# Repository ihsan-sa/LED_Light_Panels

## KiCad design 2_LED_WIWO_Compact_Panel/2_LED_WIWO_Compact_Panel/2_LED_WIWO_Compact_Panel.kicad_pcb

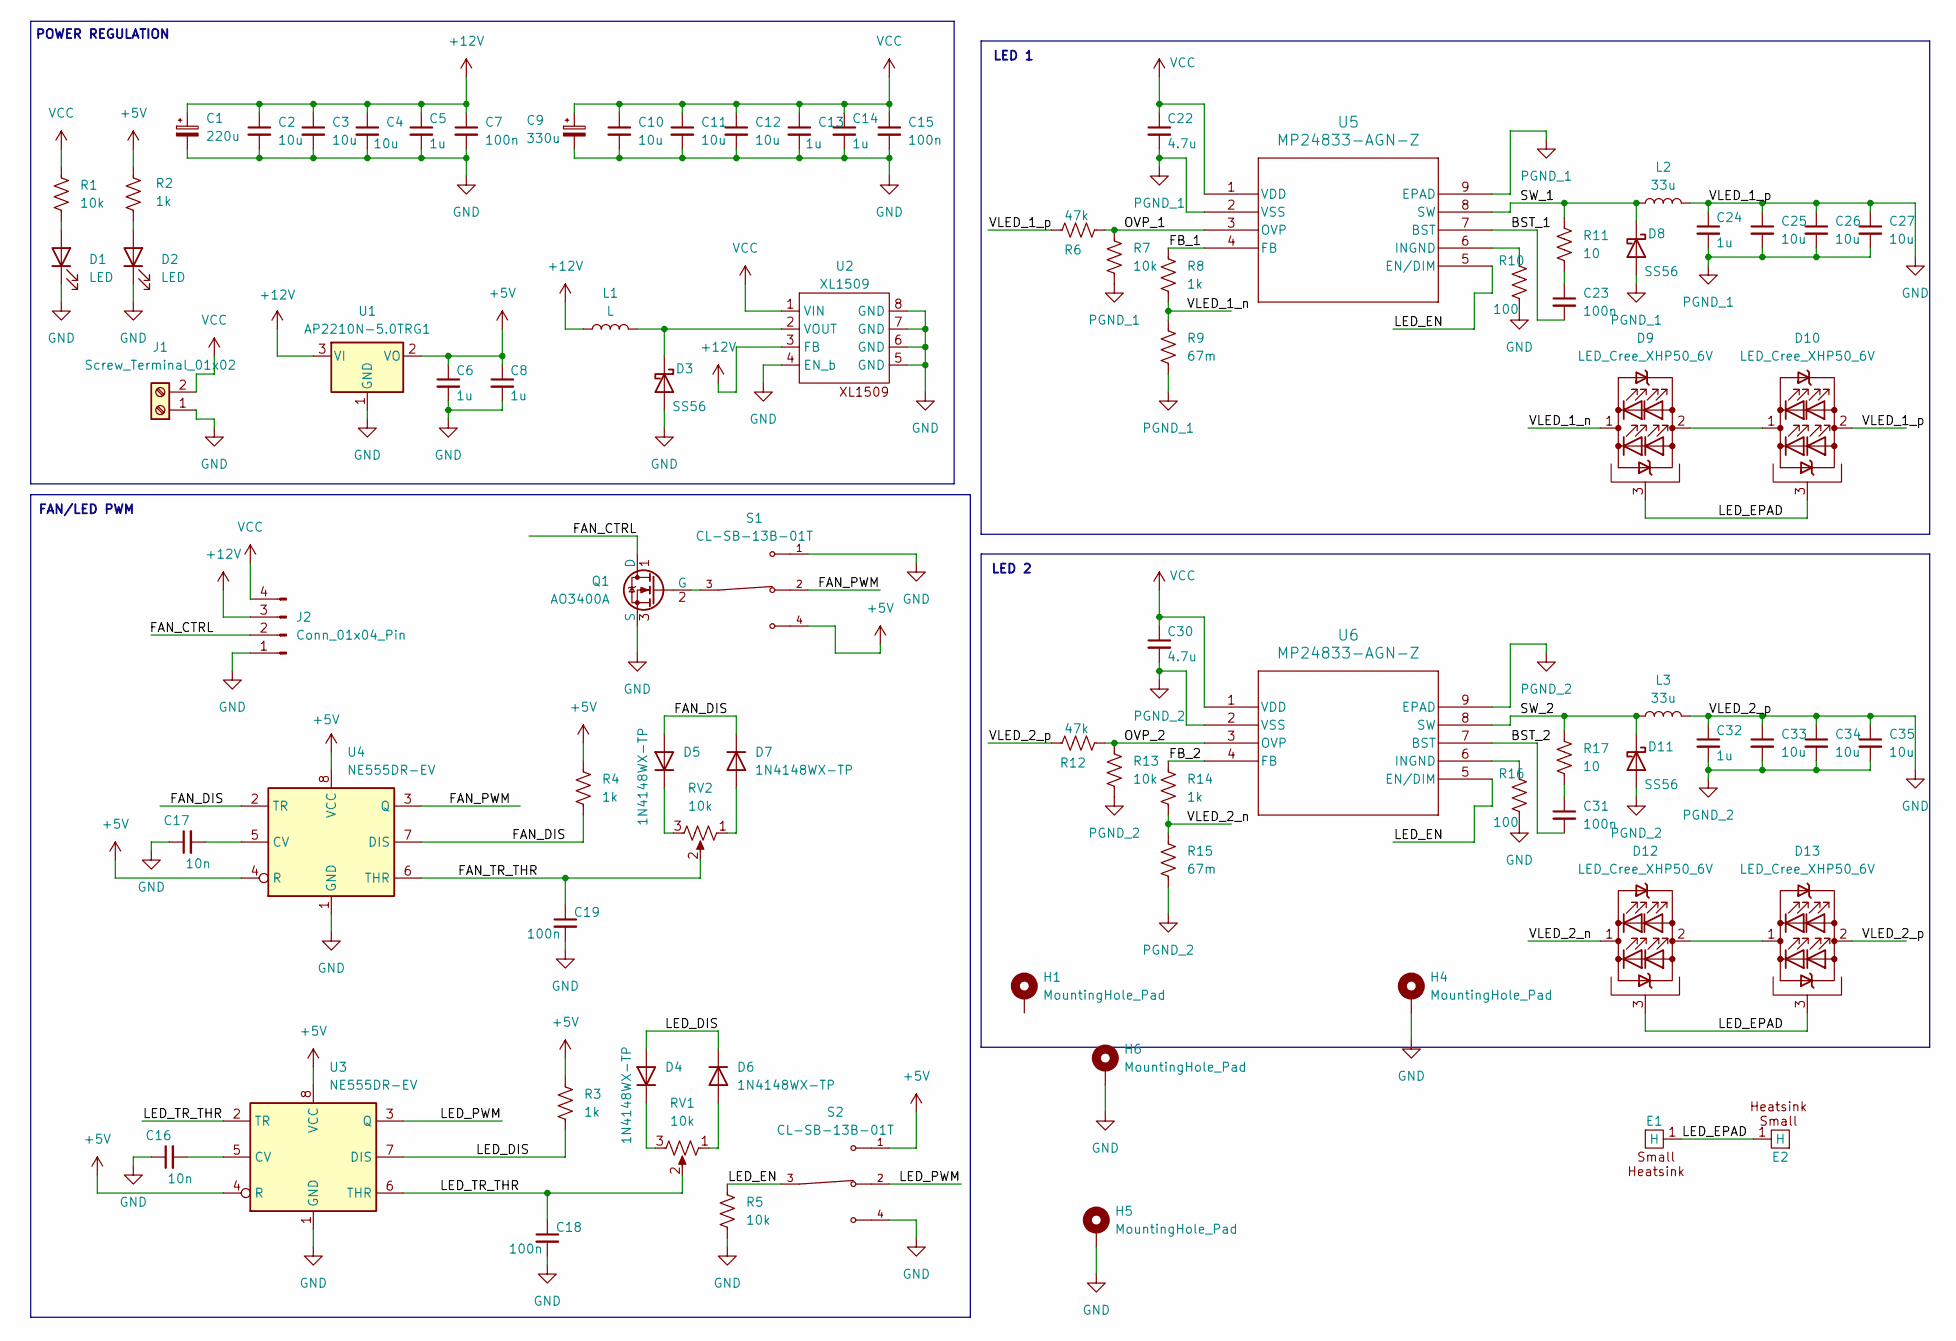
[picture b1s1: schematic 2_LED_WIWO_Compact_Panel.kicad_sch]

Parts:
C1: 220u; CAP_6.3 X 7.7_PAN
C2, C3, C4, C10, C11, C12, C25, C26, C27, C33, C34, C35: 10u; C_0603_1608Metric_Pad1.08x0.95mm_HandSolder
C5, C6, C8, C13, C14: 1u; C_0402_1005Metric_Pad0.74x0.62mm_HandSolder
C7, C15: 100n; C_0201_0603Metric_Pad0.64x0.40mm_HandSolder
C9: 330u; CAPAE1030X1050N
C16, C17: 10n; R_0201_0603Metric_Pad0.64x0.40mm_HandSolder
C18, C19: 100n; R_0402_1005Metric_Pad0.72x0.64mm_HandSolder
C22, C30: 4.7u; C_0603_1608Metric_Pad1.08x0.95mm_HandSolder
C23, C31: 100n; C_0603_1608Metric_Pad1.08x0.95mm_HandSolder
C24, C32: 1u; C_0603_1608Metric_Pad1.08x0.95mm_HandSolder
D1, D2: LED; LED_0603_1608Metric_Pad1.05x0.95mm_HandSolder
D3, D8, D11: SS56; D_SMA_Handsoldering
D4, D5, D6, D7: 1N4148WX-TP; D_SOD-323_HandSoldering
D9, D10, D12, D13: LED_Cree_XHP50_6V; LED_Cree-XHP50_6V
E1, E2: small_heatsink
H1, H4, H5, H6: MountingHole_Pad; MountingHole_3.2mm_M3_Pad
J1: Screw_Terminal_01x02; TerminalBlock_MaiXu_MX126-5.0-02P_1x02_P5.00mm
J2: Conn_01x04_Pin; PinHeader_1x04_P2.54mm_Vertical
L1: L; CDRH127L125NP-680MC
L2, L3: 33u; IND_SRP1265A-330M
Q1: AO3400A; SOT-23_Handsoldering
R1, R5, R7, R13: 10k; R_0402_1005Metric_Pad0.72x0.64mm_HandSolder
R2, R3, R4, R8, R14: 1k; R_0402_1005Metric_Pad0.72x0.64mm_HandSolder
R6, R12: 47k; R_0402_1005Metric_Pad0.72x0.64mm_HandSolder
R9, R15: 67m; R_2512_6332Metric_Pad1.40x3.35mm_HandSolder
R10, R16: 100; R_0603_1608Metric_Pad0.98x0.95mm_HandSolder
R11, R17: 10; R_0603_1608Metric_Pad0.98x0.95mm_HandSolder
RV1, RV2: 10k; PTV09A-4015F-B104_BRN
S1, S2: CL-SB-13B-01T; SW_CL-SB-13B-01T; PARTREV N/A
U1: AP2210N-5.0TRG1; TSOT-23
U2: XL1509; SOIC-8_3.9x4.9mm_P1.27mm
U3, U4: NE555DR-EV; SOIC-8_3.9x4.9mm_P1.27mm
U5, U6: MP24833-AGN-Z; SOIC-8-1EP_3.9x4.9mm_P1.27mm_EP2.514x3.2mm_ThermalVias

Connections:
+5V: C6.1, C8.1, R2.1, R3.1, R4.1, S1.4, S2.1, U1.2 (VO), U3.4 (R), U3.8 (VCC), U4.4 (R), U4.8 (VCC)
+12V: C1.1, C2.1, C3.1, C4.1, C5.1, C7.1, J2.3, L1.1, U1.3 (VI), U2.3 (FB)
/BST_1: C23.2, U5.7 (BST)
/BST_2: C31.2, U6.7 (BST)
/FAN_CTRL: J2.2, Q1.1 (D)
/FAN_DIS: D5.2 (A), D7.1 (K), R4.2, U4.2 (TR), U4.7 (DIS)
/FAN_PWM: S1.2, U4.3 (Q)
/FAN_TR_THR: C19.1, RV2.2, U4.6 (THR)
/FB_1: R8.1, U5.4 (FB)
/FB_2: R14.1, U6.4 (FB)
/LED_DIS: D4.2 (A), D6.1 (K), R3.2, U3.7 (DIS)
/LED_EN: R5.1, S2.3, U5.5 (EN/DIM), U6.5 (EN/DIM)
/LED_EPAD: D9.3 (PAD), D10.3 (PAD), D12.3 (PAD), D13.3 (PAD), E1.1 (H), E2.1 (H)
/LED_PWM: S2.2, U3.3 (Q)
/LED_TR_THR: C18.1, RV1.2, U3.2 (TR), U3.6 (THR)
/OVP_1: R6.2, R7.1, U5.3 (OVP)
/OVP_2: R12.2, R13.1, U6.3 (OVP)
/SW_1: D8.1 (K), L2.1, R11.1, U5.8 (SW)
/SW_2: D11.1 (K), L3.1, R17.1, U6.8 (SW)
/VLED_1_n: D9.1 (K), R8.2, R9.1
/VLED_2_n: D12.1 (K), R14.2, R15.1
GND: C1.2, C2.2, C3.2, C4.2, C5.2, C6.2, C7.2, C8.2, C9.2, C10.2, C11.2, C12.2, C13.2, C14.2, C15.2, C16.1, C17.1, C18.2, C19.2, C24.1, C25.1, C26.1, C27.1, C32.1, C33.1, C34.1, C35.1, D1.1 (K), D2.1 (K), D3.2 (A), D10.2 (A), D13.2 (A), H4.1, H5.1, H6.1, J1.1, J2.1, L2.2, L3.2, Q1.3 (S), R5.2, R6.1, R10.2, R12.1, R16.2, S1.1, S2.4, U1.1 (GND), U2.4 (EN_b), U2.5 (GND), U2.6 (GND), U2.7 (GND), U2.8 (GND), U3.1 (GND), U4.1 (GND)
unnamed: C23.1, R11.2
unnamed: C31.1, R17.2
unnamed: D1.2 (A), R1.2
unnamed: D2.2 (A), R2.2
unnamed: D3.1 (K), L1.2, U2.2 (VOUT)
unnamed: D4.1 (K), RV1.3
unnamed: D5.1 (K), RV2.3
unnamed: D6.2 (A), RV1.1
unnamed: D7.2 (A), RV2.1
unnamed: D9.2 (A), D10.1 (K)
unnamed: D12.2 (A), D13.1 (K)
unnamed: Q1.2 (G), S1.3
unnamed: C16.2, U3.5 (CV)
unnamed: C17.2, U4.5 (CV)
unnamed: R10.1, U5.6 (INGND)
unnamed: R16.1, U6.6 (INGND)
PGND_1: C22.2, C24.2, C25.2, C26.2, C27.2, D8.2 (A), R7.2, R9.2, U5.2 (VSS), U5.9 (EPAD)
PGND_2: C30.2, C32.2, C33.2, C34.2, C35.2, D11.2 (A), R13.2, R15.2, U6.2 (VSS), U6.9 (EPAD)
VCC: C9.1, C10.1, C11.1, C12.1, C13.1, C14.1, C15.1, C22.1, C30.1, J1.2, J2.4, R1.1, U2.1 (VIN), U5.1 (VDD), U6.1 (VDD)

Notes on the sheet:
FAN/LED PWM
LED 1
LED 2
POWER REGULATION

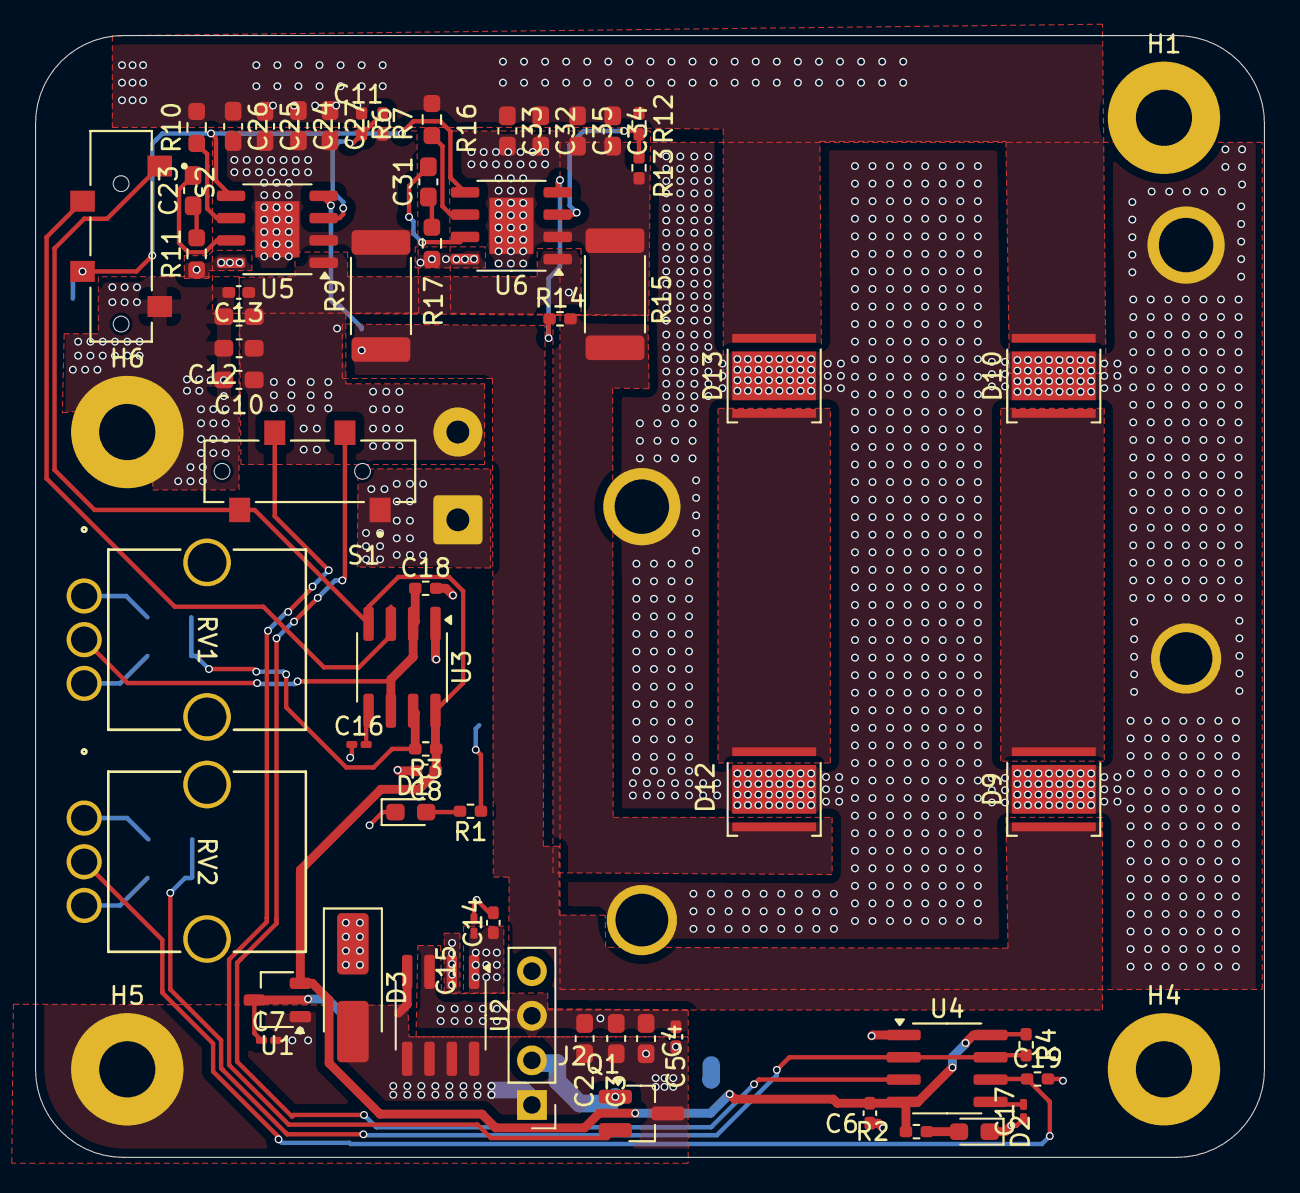
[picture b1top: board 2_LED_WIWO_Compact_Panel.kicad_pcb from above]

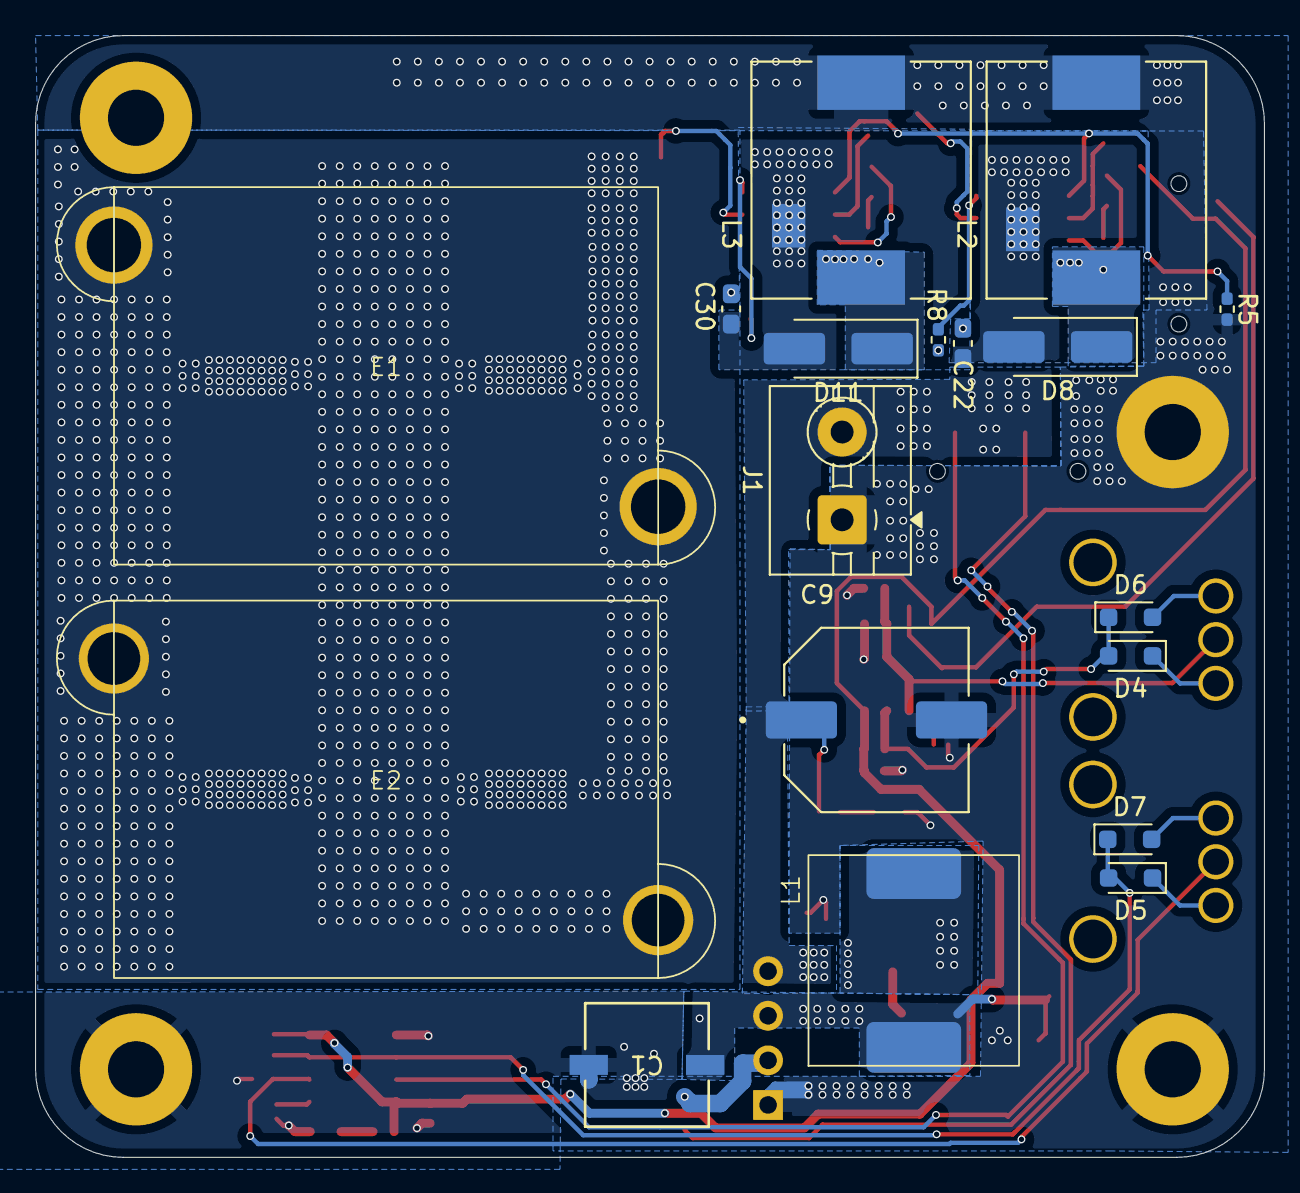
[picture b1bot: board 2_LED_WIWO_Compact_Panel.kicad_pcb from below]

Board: 2 copper layers, 70.0 x 63.9 mm, 83 parts (18 on the bottom side), 41 nets.

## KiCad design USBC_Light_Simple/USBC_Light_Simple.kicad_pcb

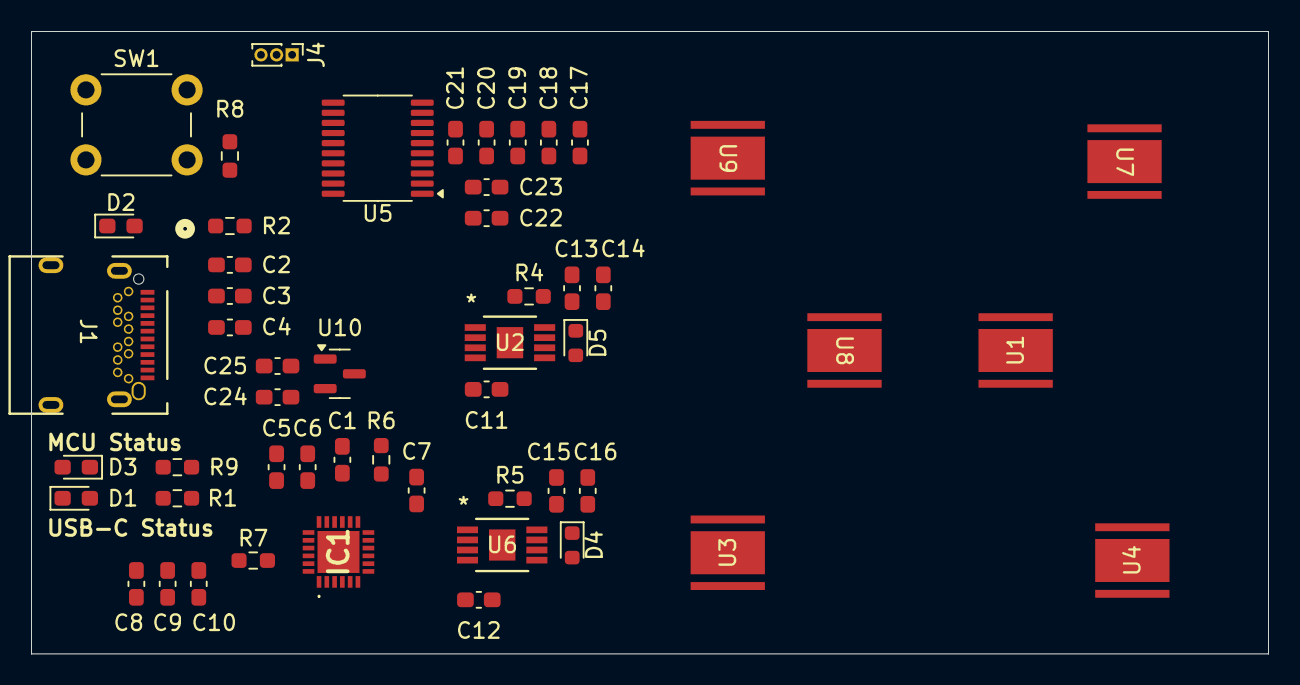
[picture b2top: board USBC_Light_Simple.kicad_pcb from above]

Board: 2 copper layers, 79.5 x 40.0 mm, 52 parts (0 on the bottom side), 37 nets, no tracks yet.

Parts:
C1, C4, C6, C7, C10, C11, C12, C13, C15, C19, C20, C25: 100n; C_0603_1608Metric_Pad1.08x0.95mm_HandSolder
C2, C8: 10u; C_0603_1608Metric_Pad1.08x0.95mm_HandSolder
C3, C5, C9, C14, C16, C17, C18, C24: 1u; C_0603_1608Metric_Pad1.08x0.95mm_HandSolder
C21: 10n; C_0603_1608Metric_Pad1.08x0.95mm_HandSolder
C22, C23: *; C_0603_1608Metric_Pad1.08x0.95mm_HandSolder
D1, D2, D3: LED; LED_0603_1608Metric_Pad1.05x0.95mm_HandSolder
D4, D5: D; D_0603_1608Metric
IC1: AP33772SDKZ-13-FA01; AP33772SDKZ13FA01
J1: USB_C_Receptacle; CONN24_4056-03-A_GCT
J4: Screw_Terminal_01x03; PinHeader_1x03_P1.00mm_Vertical
R1, R9: 1k; R_0603_1608Metric_Pad0.98x0.95mm_HandSolder
R2: 100k; R_0603_1608Metric_Pad0.98x0.95mm_HandSolder
R4, R5: RS; R_0603_1608Metric_Pad0.98x0.95mm_HandSolder
R6, R8: 10k; R_0603_1608Metric_Pad0.98x0.95mm_HandSolder
R7: 100; R_0603_1608Metric_Pad0.98x0.95mm_HandSolder
SW1: SW_Push; SW_PUSH_6mm
U1, U3, U4, U7, U8, U9: XHP50B-00-0000-0D0BJ440E; CHIP_D0BJ440E_WFS
U2, U6: AL8861MP-13; MSOP-8EP_DIO
U5: STM32C011F6Px; TSSOP-20_4.4x6.5mm_P0.65mm
U10: AP2127N-3.3; SOT-23

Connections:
+3V3: C17.1, C18.1, C19.1, C20.1, C21.1, C24.1, C25.1, R8.1, U5.4 (VDD), U10.2 (VO)
+5V: C5.1, C6.1, IC1.20 (V5V), U10.3 (VI)
+18V: C7.1, IC1.12 (V18)
/LEDs/LED_1: R4.2, U2.1 (ISENSE), U9.1
/LEDs/LED_2: R5.2, U1.1, U6.1 (ISENSE)
/LEDs/LX_1: D5.2 (A), U2.5 (LX), U2.6 (LX)
/LEDs/LX_2: D4.2 (A), U6.5 (LX), U6.6 (LX)
/LEDs/Thermal_Pad: U1.2, U3.2, U4.2, U7.2, U8.2, U9.2
/LEDs/VSET_1: C11.1, U2.4 (VSET)
/LEDs/VSET_2: C12.1, U6.4 (VSET)
/MCU/I2C_SCL: IC1.5 (SCL), U5.20 (PB6)
/MCU/I2C_SDA: IC1.4 (SDA), U5.1 (PB7)
/MCU/NRST: R8.2, SW1.2, U5.6 (PF2)
/MCU/OSC_IN: C22.2, U5.2 (PC14)
/MCU/OSC_OUT: C23.2, U5.3 (PC15)
/MCU/STATUS_LED: D3.2 (A), U5.11 (PA4)
/MCU/UART_RX: J4.3, U5.8 (PA1)
/MCU/UART_TX: J4.2, U5.7 (PA0)
/USB_C_IC/CC1: IC1.17 (CC1), J1.A5 (CC1)
/USB_C_IC/CC2: IC1.16 (CC2), J1.B5 (CC2)
/USB_C_IC/VOUT: C8.1, C9.1, C10.1, R7.1
/USB_C_IC/data_+: IC1.19 (DP), J1.A6 (D+), J1.B6 (D+)
/USB_C_IC/data_-: IC1.18 (DN), J1.A7 (D-), J1.B7 (D-)
GND: C1.2, C2.2, C3.2, C4.2, C5.2, C6.2, C7.2, C8.2, C9.2, C10.2, C11.2, C12.2, C13.2, C14.2, C15.2, C16.2, C17.2, C18.2, C19.2, C20.2, C21.2, C22.1, C23.1, C24.2, C25.2, D1.1 (K), D2.1 (K), IC1.3 (GND_1), IC1.25 (GND_2), J1.A1 (GND), J1.A12 (GND), J1.B1 (GND), J1.B12 (GND), J4.1, R6.2, R9.1, SW1.1, U2.2 (GND), U2.3 (GND), U5.5 (VSS), U6.2 (GND), U6.3 (GND), U10.1 (GND)
unnamed: D1.2 (A), R1.1
unnamed: D2.2 (A), R2.2
unnamed: D3.1 (K), R9.2
unnamed: C1.1, IC1.15 (IFB)
unnamed: IC1.8 (LED), R1.2
unnamed: IC1.13 (OTP), R6.1
unnamed: IC1.22 (VOUT), R7.2
unnamed: U1.3, U3.1
unnamed: U3.3, U4.1
unnamed: U7.1, U8.3
unnamed: U8.1, U9.3
VBUS: C2.1, C3.1, C4.1, IC1.1 (ISENP), J1.A4 (VBUS), J1.A9 (VBUS), J1.B4 (VBUS), J1.B9 (VBUS), R2.1
VLED: C13.1, C14.1, C15.1, C16.1, D4.1 (K), D5.1 (K), R4.1, R5.1, U2.8 (VIN), U6.8 (VIN)

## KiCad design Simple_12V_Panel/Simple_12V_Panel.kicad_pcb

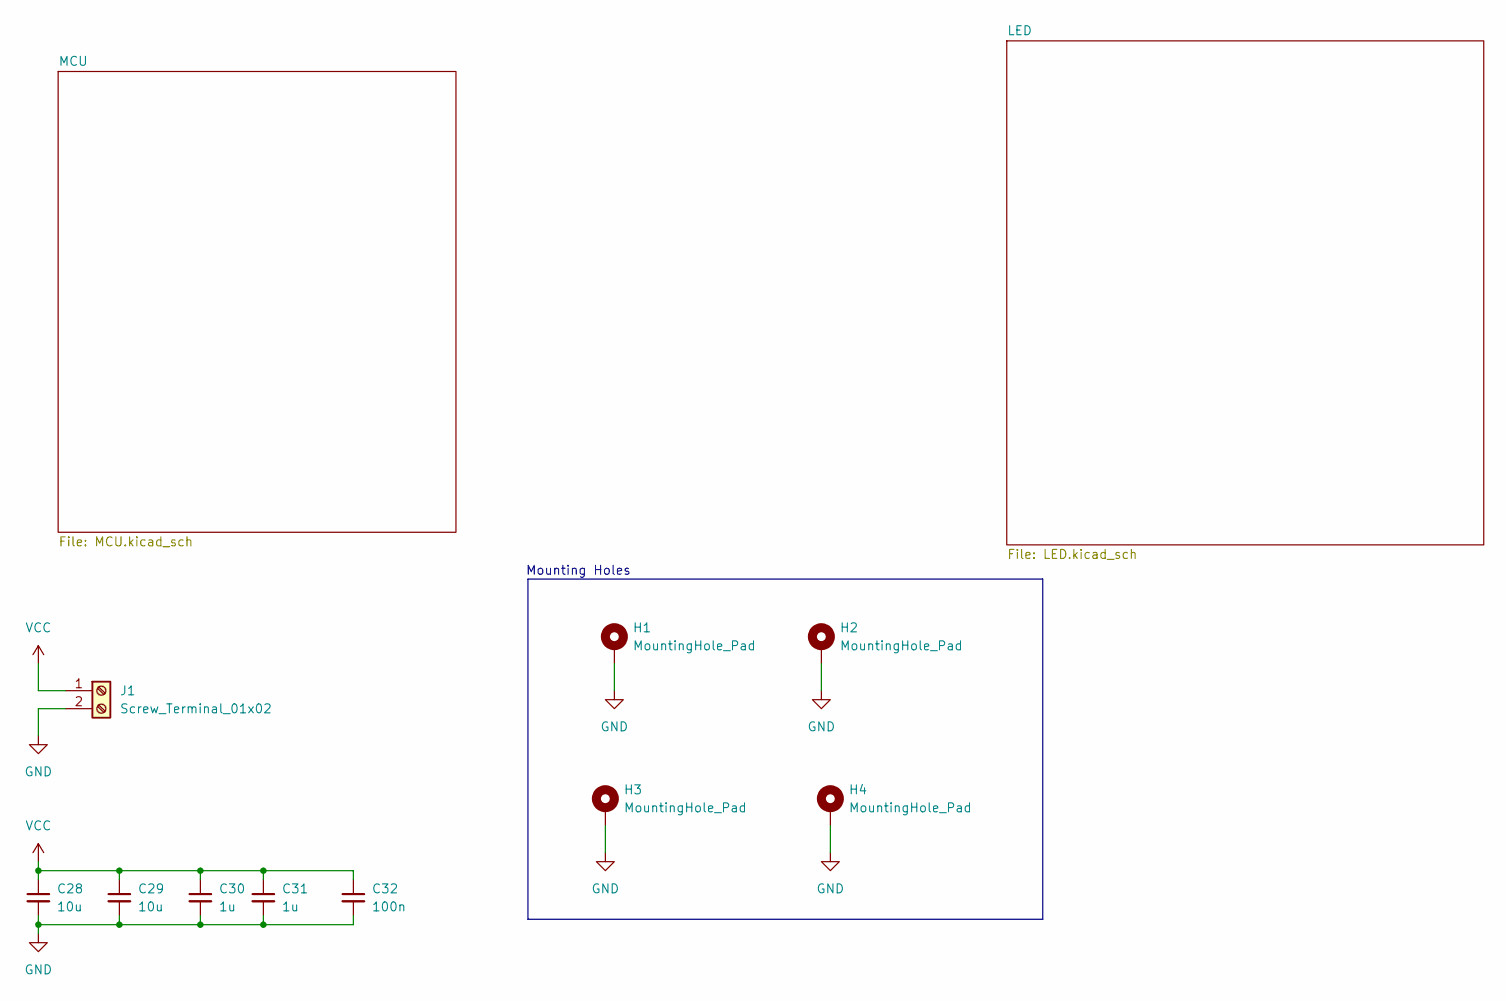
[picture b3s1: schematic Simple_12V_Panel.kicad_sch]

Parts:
C28, C29: 10u; C_0603_1608Metric_Pad1.08x0.95mm_HandSolder
C30, C31: 1u; C_0603_1608Metric_Pad1.08x0.95mm_HandSolder
C32: 100n; C_0603_1608Metric_Pad1.08x0.95mm_HandSolder
H1, H2, H3, H4: MountingHole_Pad; MountingHole_3.2mm_M3_Pad
J1: Screw_Terminal_01x02; TerminalBlock_MaiXu_MX126-5.0-02P_1x02_P5.00mm

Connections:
GND: C28.2, C29.2, C30.2, C31.2, C32.2, H1.1, H2.1, H3.1, H4.1, J1.2; also elsewhere on the board
VCC: C28.1, C29.1, C30.1, C31.1, C32.1, J1.1; also elsewhere on the board

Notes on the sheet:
Mounting Holes

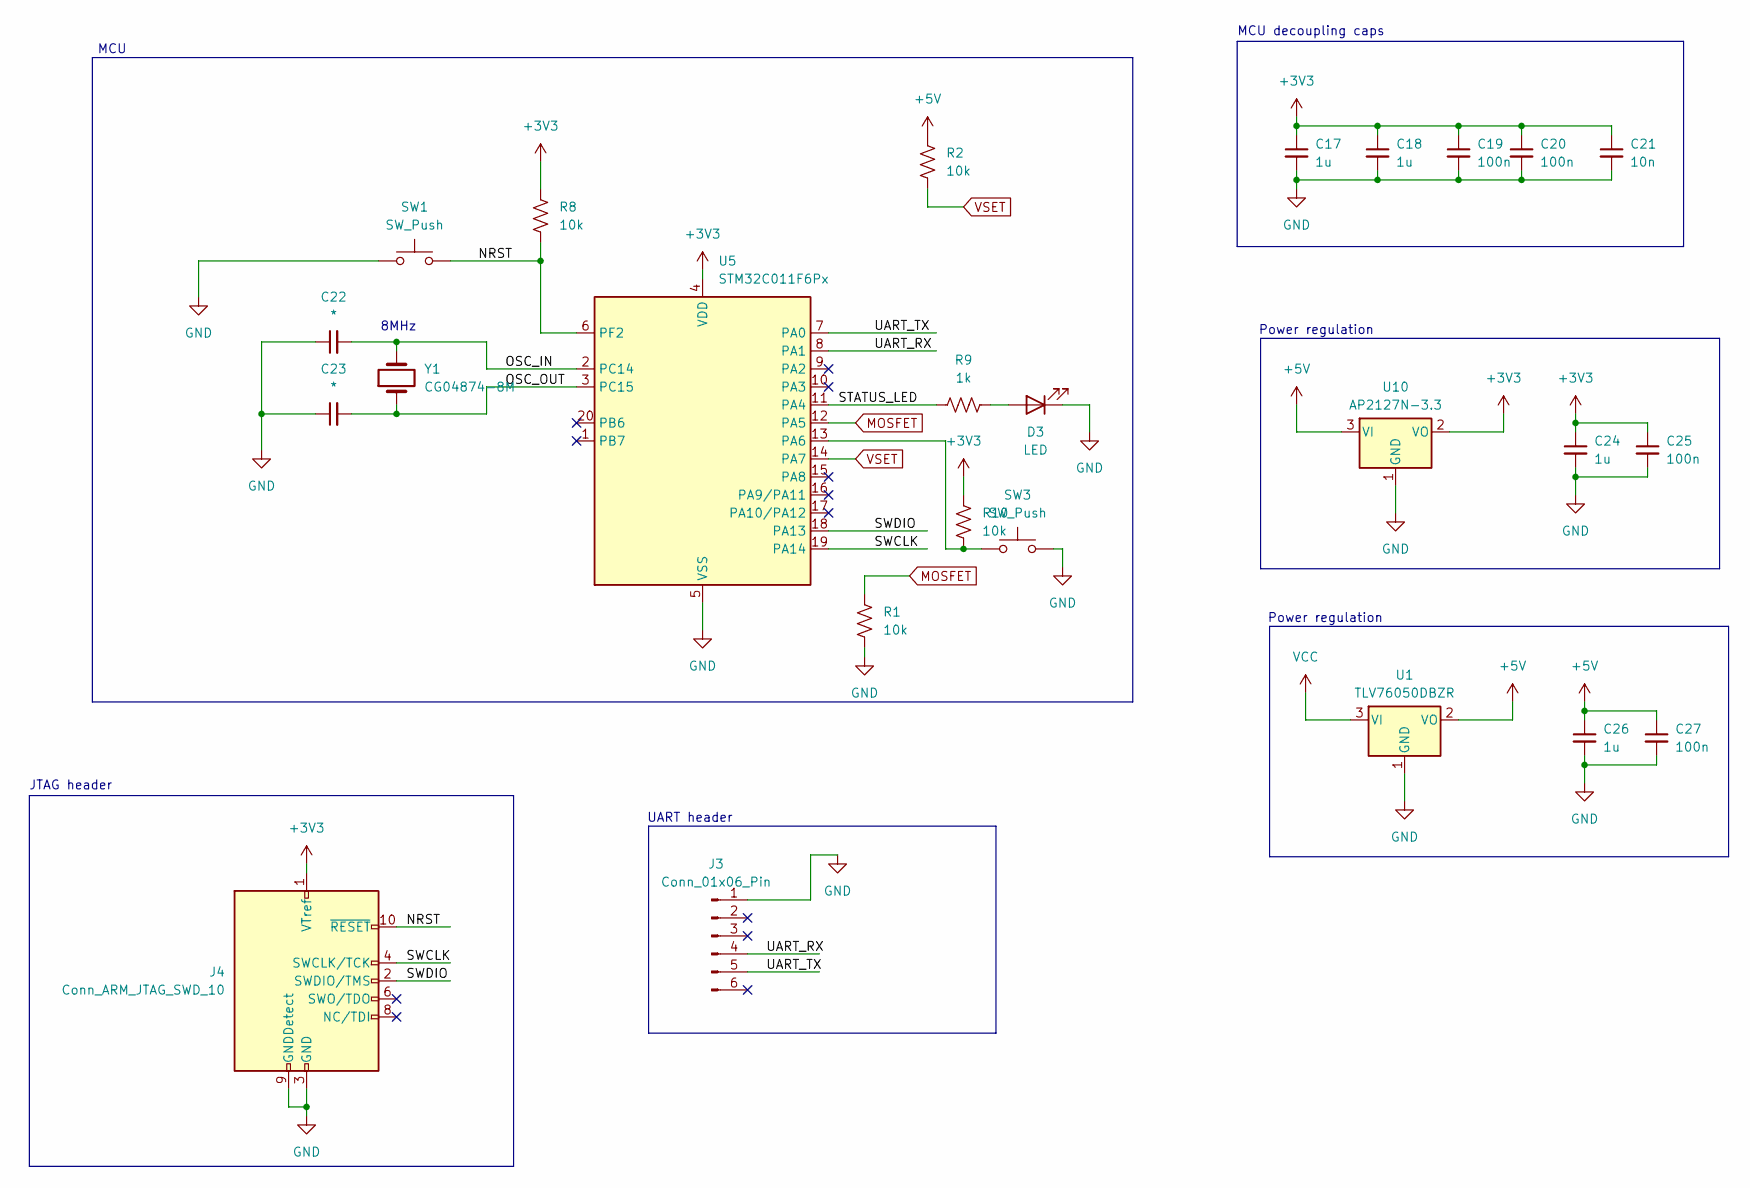
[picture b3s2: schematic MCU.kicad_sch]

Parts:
C17, C18, C24, C26: 1u; C_0603_1608Metric_Pad1.08x0.95mm_HandSolder
C19, C20, C25, C27: 100n; C_0603_1608Metric_Pad1.08x0.95mm_HandSolder
C21: 10n; C_0603_1608Metric_Pad1.08x0.95mm_HandSolder
C22, C23: *; C_0603_1608Metric_Pad1.08x0.95mm_HandSolder
D3: LED; LED_0603_1608Metric_Pad1.05x0.95mm_HandSolder
J3: Conn_01x06_Pin; PinHeader_1x06_P2.54mm_Vertical
J4: Conn_ARM_JTAG_SWD_10; PinHeader_2x05_P1.27mm_Vertical
R1, R2, R8, R10: 10k; R_0603_1608Metric_Pad0.98x0.95mm_HandSolder
R9: 1k; R_0603_1608Metric_Pad0.98x0.95mm_HandSolder
SW1, SW3: SW_Push; SW_PUSH_6mm
U1: TLV76050DBZR; SOT-23-3
U5: STM32C011F6Px; TSSOP-20_4.4x6.5mm_P0.65mm
U10: AP2127N-3.3; SOT-23
Y1: CG04874-8M; XTAL_CG04874_NDK

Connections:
+3V3: C17.1, C18.1, C19.1, C20.1, C21.1, C24.1, C25.1, J4.1 (VTref), R8.1, R10.1, U5.4 (VDD), U10.2 (VO)
+5V: C26.1, C27.1, R2.1, U1.2 (VO), U10.3 (VI)
/MCU/NRST: J4.10 (~RESET), R8.2, SW1.2, U5.6 (PF2)
/MCU/OSC_IN: C22.2, U5.2 (PC14), Y1.2
/MCU/OSC_OUT: C23.2, U5.3 (PC15), Y1.1
/MCU/STATUS_LED: R9.2, U5.11 (PA4)
/MCU/SWCLK: J4.4 (SWCLK/TCK), U5.19 (PA14)
/MCU/SWDIO: J4.2 (SWDIO/TMS), U5.18 (PA13)
/MCU/UART_RX: J3.4, U5.8 (PA1)
/MCU/UART_TX: J3.5, U5.7 (PA0)
GND: C17.2, C18.2, C19.2, C20.2, C21.2, C22.1, C23.1, C24.2, C25.2, C26.2, C27.2, D3.1 (K), J3.1, J4.3 (GND), J4.5 (GND), J4.9 (GNDDetect), R1.2, SW1.1, SW3.2, U1.1 (GND), U5.5 (VSS), U10.1 (GND); also elsewhere on the board
MOSFET: R1.1, U5.12 (PA5); also elsewhere on the board
unnamed: D3.2 (A), R9.1
unnamed: R10.2, SW3.1, U5.13 (PA6)
VCC: U1.3 (VI); also elsewhere on the board
VSET: R2.2, U5.14 (PA7); also elsewhere on the board

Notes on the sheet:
Power regulation
JTAG header
UART header
8MHz
MCU decoupling caps
MCU

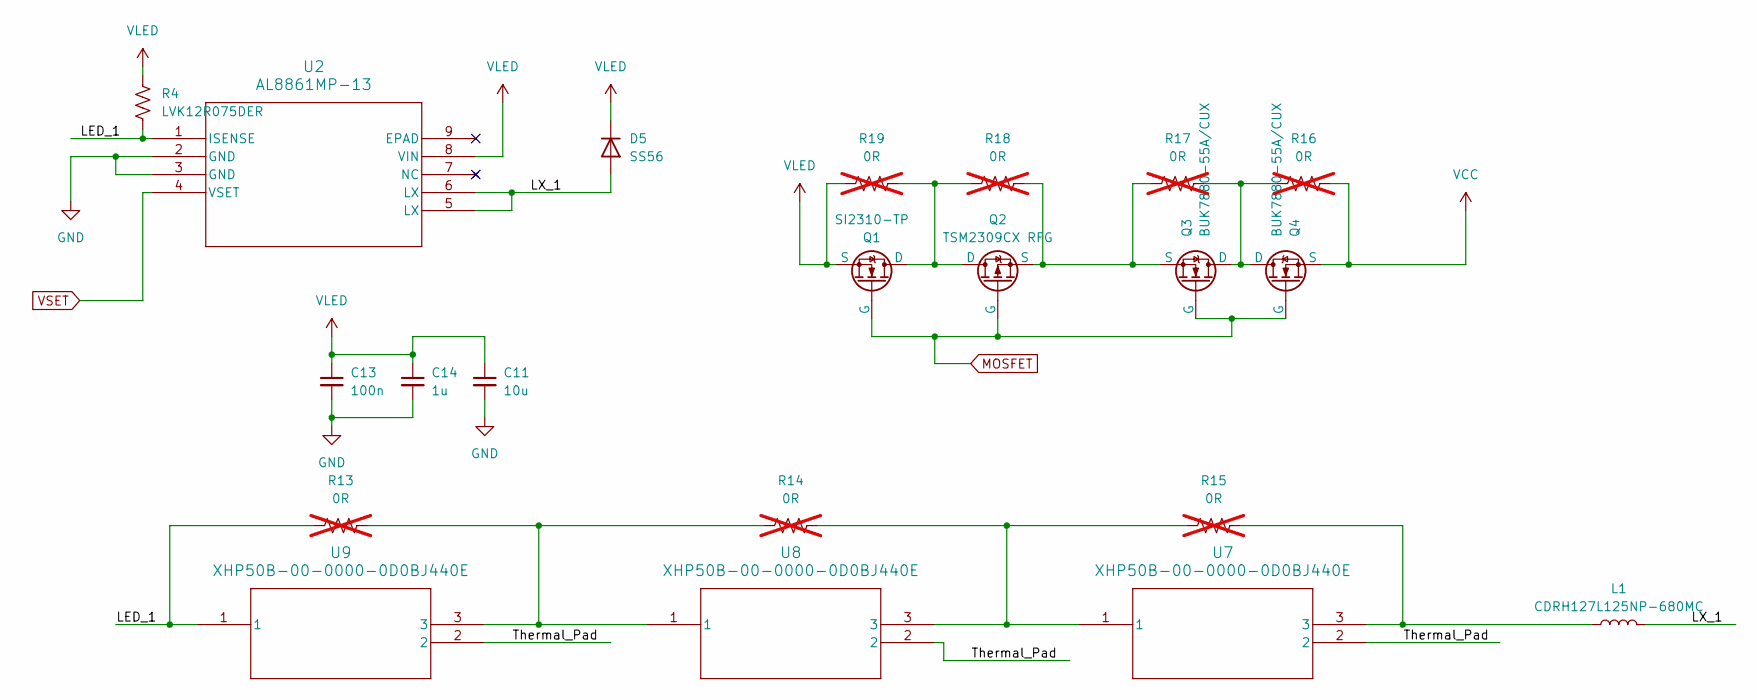
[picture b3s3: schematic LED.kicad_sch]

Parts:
C11: 10u; C_0603_1608Metric_Pad1.08x0.95mm_HandSolder
C13: 100n; C_0603_1608Metric_Pad1.08x0.95mm_HandSolder
C14: 1u; C_0603_1608Metric_Pad1.08x0.95mm_HandSolder
D5: SS56; D_SMA_Handsoldering
L1: CDRH127L125NP-680MC
Q1: SI2310-TP; SOT-23
Q2: TSM2309CX RFG; SOT-23
Q3, Q4: BUK7880-55A/CUX; SOT-223-3_TabPin2
R4: LVK12R075DER; R_1206_3216Metric_Pad1.30x1.75mm_HandSolder
R13, R14, R15, R16, R17, R18, R19: 0R; R_1206_3216Metric_Pad1.30x1.75mm_HandSolder; not fitted
U2: AL8861MP-13; MSOP-8EP_DIO
U7, U8, U9: XHP50B-00-0000-0D0BJ440E; CHIP_D0BJ440E_WFS

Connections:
/LED/LED_1: R4.2, R13.2, U2.1 (ISENSE), U9.1
/LED/LX_1: D5.2 (A), L1.2, U2.5 (LX), U2.6 (LX)
/LED/Thermal_Pad: U7.2, U8.2, U9.2
GND: C11.2, C13.2, C14.2, U2.2 (GND), U2.3 (GND), U2.EPAD; also elsewhere on the board
MOSFET: Q1.2 (G), Q2.2 (G), Q3.2 (G), Q4.2 (G); also elsewhere on the board
unnamed: L1.1, R15.1, U7.3
unnamed: Q1.1 (D), Q2.1 (D), R18.2, R19.1
unnamed: Q2.3 (S), Q3.3 (S), R17.2, R18.1
unnamed: Q3.1 (D), Q4.1 (D), R16.2, R17.1
unnamed: R13.1, R14.2, U8.1, U9.3
unnamed: R14.1, R15.2, U7.1, U8.3
VCC: Q4.3 (S), R16.1; also elsewhere on the board
VLED: C11.1, C13.1, C14.1, D5.1 (K), Q1.3 (S), R4.1, R19.2, U2.8 (VIN)
VSET: U2.4 (VSET); also elsewhere on the board

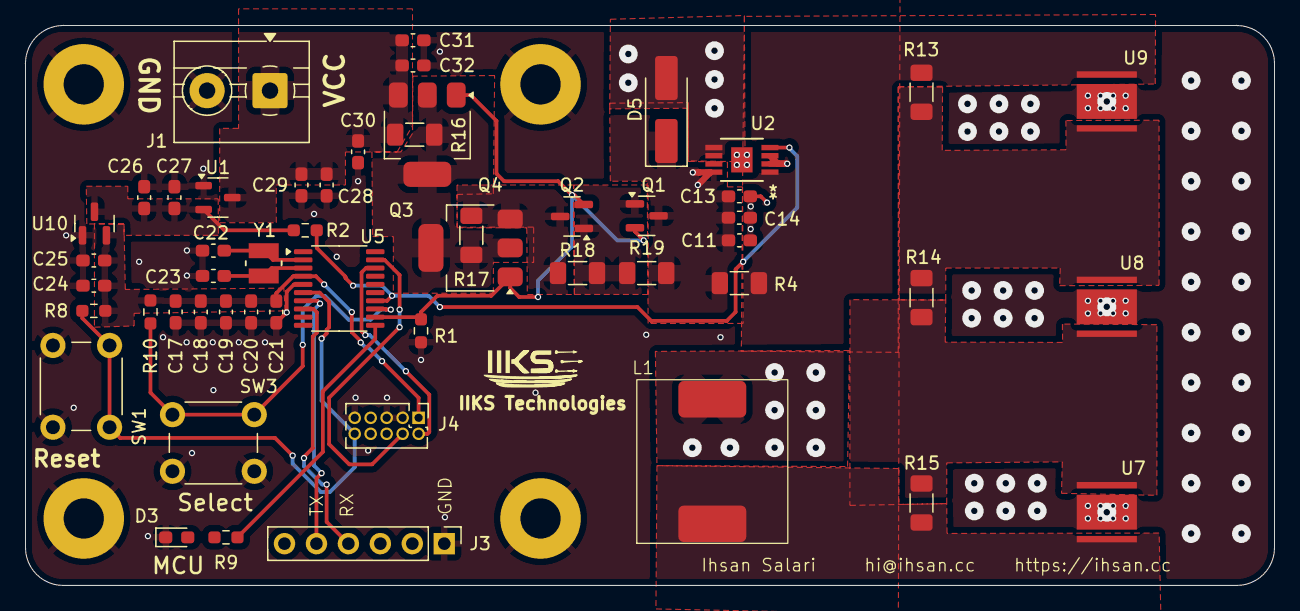
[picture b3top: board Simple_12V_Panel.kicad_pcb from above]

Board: 2 copper layers, 99.3 x 44.5 mm, 56 parts (0 on the bottom side), 26 nets.

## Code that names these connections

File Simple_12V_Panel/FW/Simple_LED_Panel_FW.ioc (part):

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Mcu.Name=STM32C011F(4-6)Px
Mcu.Package=TSSOP20
Mcu.UserName=STM32C011F6Px
PA0.Mode=Asynchronous
PA0.Signal=USART1_TX
PA1.Mode=Asynchronous
PA1.Signal=USART1_RX
PA13.Mode=Serial_Wire
PA13.Signal=DEBUG_SWDIO
PA14-BOOT0.Mode=Serial_Wire
PA14-BOOT0.Signal=DEBUG_SWCLK
PA4.Signal=S_TIM14_CH1
PA5.GPIOParameters=GPIO_Label
PA5.GPIO_Label=MOSFET
PA5.Signal=GPIO_Output
PA6.GPIOParameters=GPIO_Label,GPIO_ModeDefaultEXTI
PA6.GPIO_Label=BTN_INT
PA6.GPIO_ModeDefaultEXTI=GPIO_MODE_IT_FALLING
PA6.Signal=GPXTI6
PA7.GPIOParameters=GPIO_ModeDefaultPP,GPIO_Speed,GPIO_Label
PA7.GPIO_Label=VSET
PA7.GPIO_ModeDefaultPP=GPIO_MODE_AF_PP
PA7.GPIO_Speed=GPIO_SPEED_FREQ_VERY_HIGH
PA7.Signal=S_TIM3_CH2
PC14-OSCX_IN\ (PC14).Mode=HSE-External-Oscillator-REMAPPED
PC14-OSCX_IN\ (PC14).Signal=RCC_OSCX_IN
PC15-OSCX_OUT\ (PC15).Mode=HSE-External-Oscillator-REMAPPED
PC15-OSCX_OUT\ (PC15).Signal=RCC_OSCX_OUT
RCC.HSE_VALUE=8000000
RCC.SYSCLKFreq_VALUE=12000000
board=custom

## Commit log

2025-09-14 {Simple_12V_Panel} Done.
2025-09-14 {USBC_LIght_Simple} Relocated project
2025-10-03 created new compact LED panel project
2025-10-05 finished v1 schem and moving to layout
2025-10-06 v1 route done
2025-10-06 minor changes
